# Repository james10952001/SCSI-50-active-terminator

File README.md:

# SCSI-50-active-terminator
Open source active terminator for 50 pin single ended SCSI systems. This is designed so it can be built with either the standard male connector that mates with 50 pin SCSI cables or the less common female connector needed by the OEM cable in my DECpc 486. The connector will need to be installed on the side of the board marked 'M' if you are using a male connector or 'F' if you use a female connector. The LED can be installed on either side according to preference. It is recommended to use an old style low efficiency LED to achieve a period correct look in your vintage machine, otherwise you should increase the value of R10 so that a modern LED is not obnoxiously bright.

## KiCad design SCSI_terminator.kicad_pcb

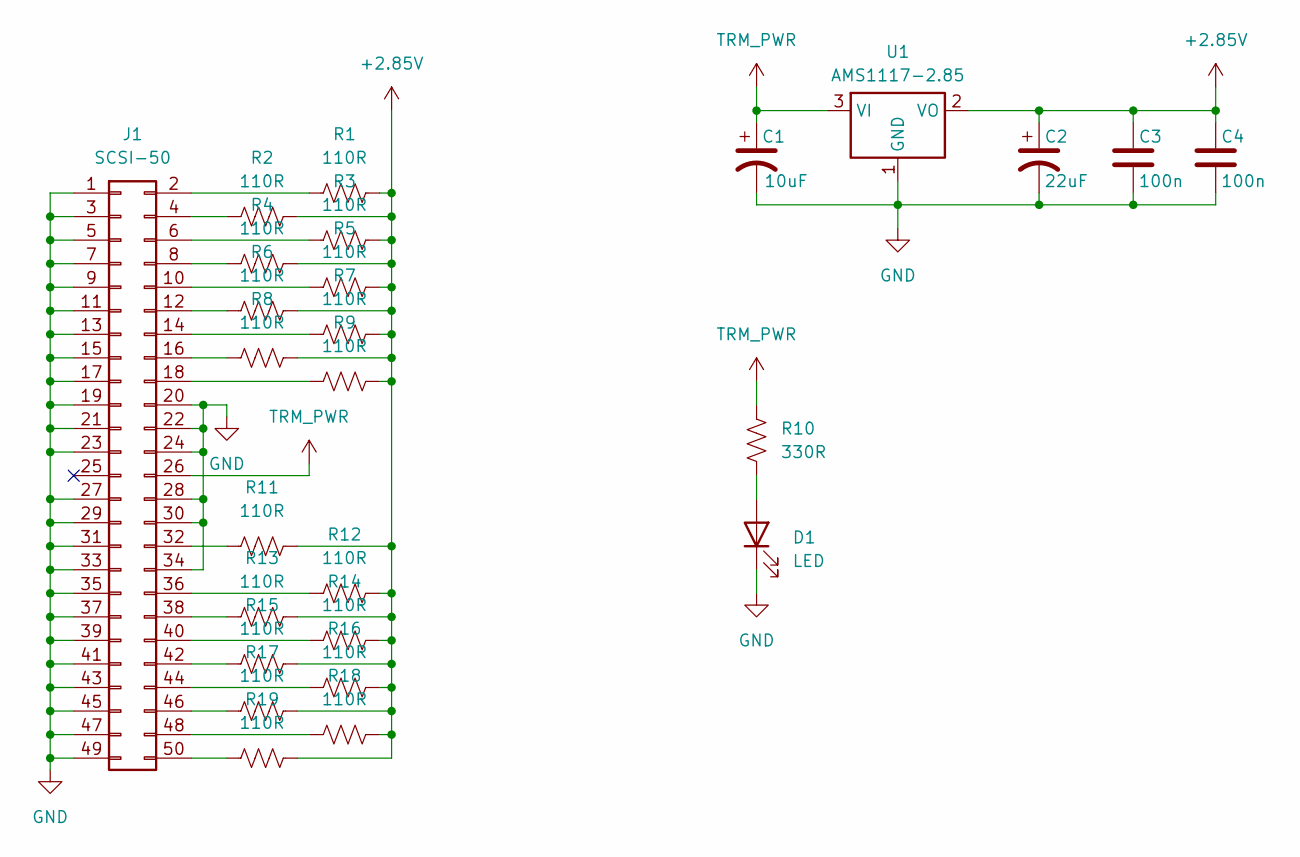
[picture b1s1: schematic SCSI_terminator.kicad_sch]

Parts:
C1: 10uF; CP_EIA-3216-18_Kemet-A
C2: 22uF; CP_EIA-3216-18_Kemet-A
C3, C4: 100n; C_0603_1608Metric
D1: LED; LED_D5.0mm
J1: SCSI-50; PinHeader_2x25_P2.54mm_Vertical
R1, R2, R3, R4, R5, R6, R7, R8, R9, R11, R12, R13, R14, R15, R16, R17, R18, R19: 110R; R_0603_1608Metric
R10: 330R; R_0603_1608Metric
U1: AMS1117-2.85; SOT-223-3_TabPin2

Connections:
+2.85V: C2.1, C3.1, C4.1, R1.2, R2.2, R3.2, R4.2, R5.2, R6.2, R7.2, R8.2, R9.2, R11.2, R12.2, R13.2, R14.2, R15.2, R16.2, R17.2, R18.2, R19.2, U1.2 (VO)
GND: C1.2, C2.2, C3.2, C4.2, D1.1 (K), J1.1, J1.3, J1.5, J1.7, J1.9, J1.11, J1.13, J1.15, J1.17, J1.19, J1.20, J1.21, J1.22, J1.23, J1.24, J1.27, J1.28, J1.29, J1.30, J1.31, J1.33, J1.34, J1.35, J1.37, J1.39, J1.41, J1.43, J1.45, J1.47, J1.49, U1.1 (GND)
unnamed: D1.2 (A), R10.1
unnamed: J1.2, R1.1
unnamed: J1.4, R2.1
unnamed: J1.6, R3.1
unnamed: J1.8, R4.1
unnamed: J1.10, R5.1
unnamed: J1.12, R6.1
unnamed: J1.14, R7.1
unnamed: J1.16, R8.1
unnamed: J1.18, R9.1
unnamed: J1.32, R11.1
unnamed: J1.36, R12.1
unnamed: J1.38, R13.1
unnamed: J1.40, R14.1
unnamed: J1.42, R15.1
unnamed: J1.44, R16.1
unnamed: J1.46, R17.1
unnamed: J1.48, R18.1
unnamed: J1.50, R19.1
TRM_PWR: C1.1, J1.26, R10.2, U1.3 (VI)

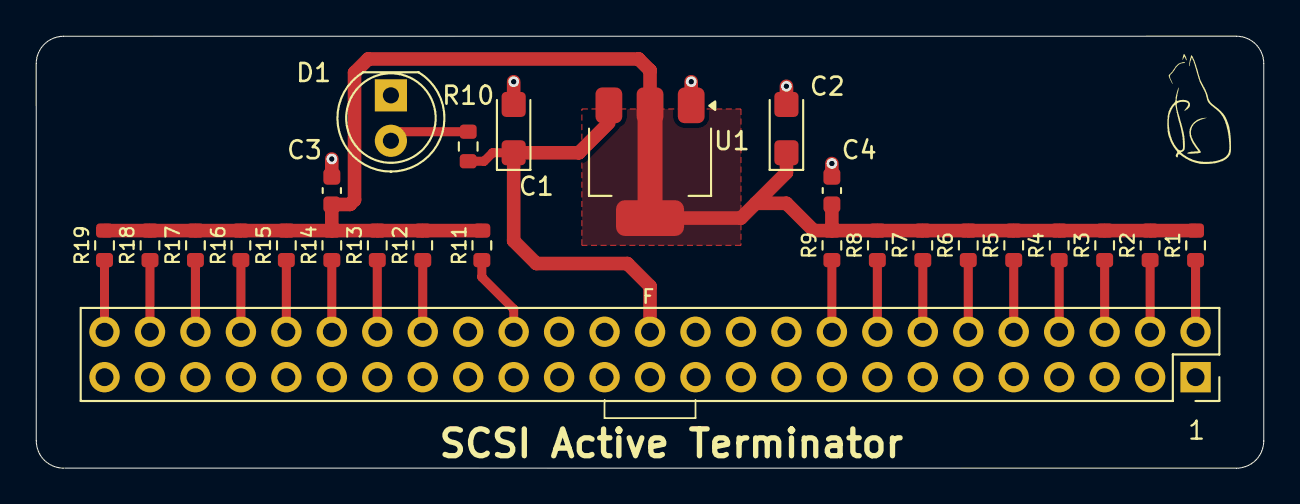
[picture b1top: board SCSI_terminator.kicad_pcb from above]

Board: 2 copper layers, 68.6 x 24.1 mm, 27 parts (1 on the bottom side), 22 nets.

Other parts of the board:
VAL: REF; cat_300

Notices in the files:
SCSI_terminator.kicad_pcb:
(c)2025 James Sweet
